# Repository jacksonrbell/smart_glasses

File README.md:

# Smart Translator Glasses
ECE 3332 - Microcontrollers Lab | Texas Tech University <br>
Jack Bell, Erik Longhenry, Brandon Runhaar

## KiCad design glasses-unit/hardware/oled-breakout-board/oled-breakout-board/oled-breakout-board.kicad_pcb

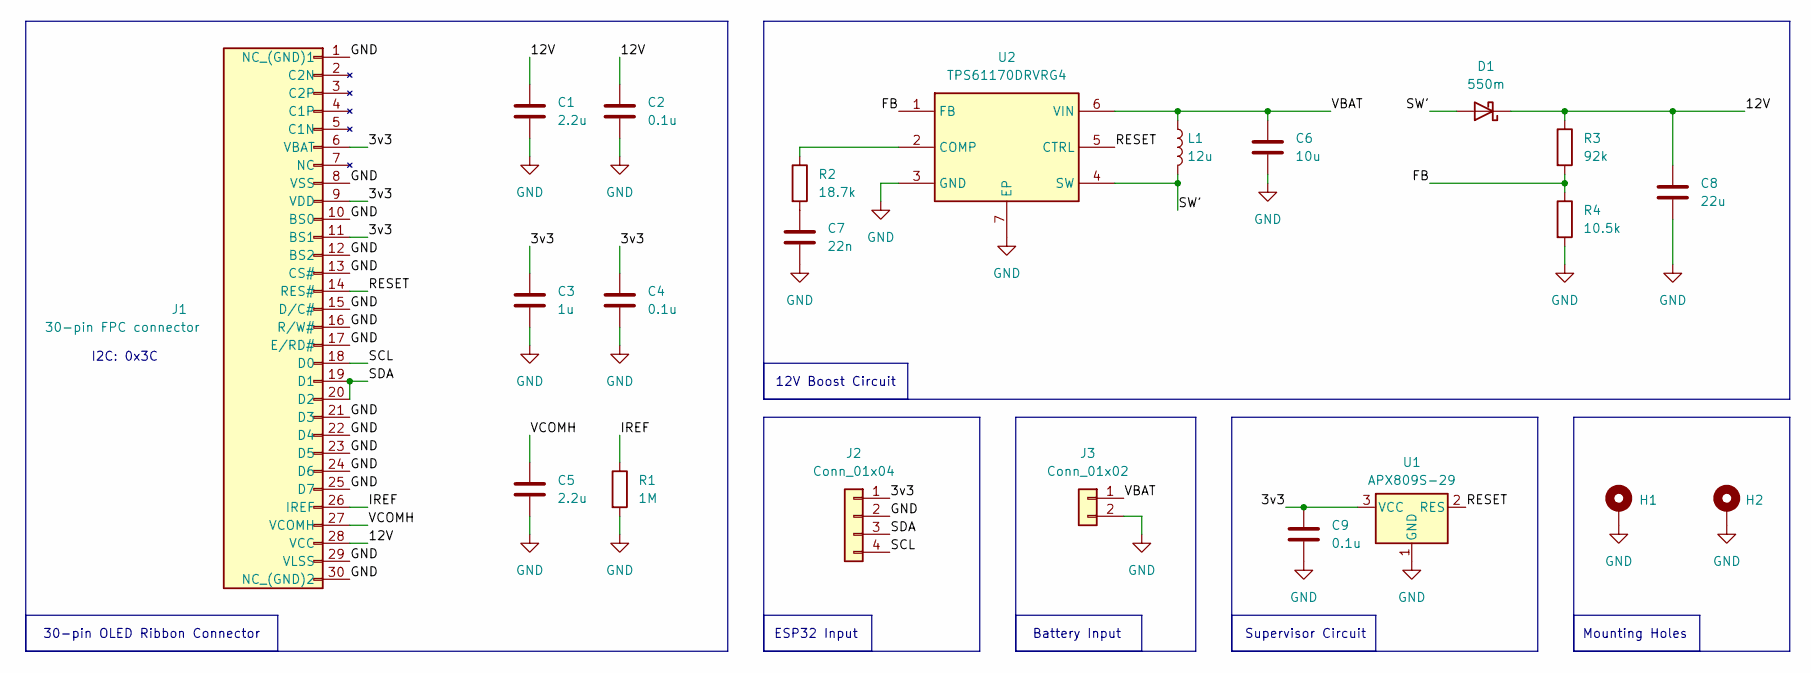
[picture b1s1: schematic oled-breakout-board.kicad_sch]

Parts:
C1, C5: 2.2u; C_1206_3216Metric_Pad1.33x1.80mm_HandSolder
C2, C4, C9: 0.1u; C_0603_1608Metric_Pad1.08x0.95mm_HandSolder
C3: 1u; C_0603_1608Metric_Pad1.08x0.95mm_HandSolder
C6: 10u; C_1206_3216Metric_Pad1.33x1.80mm_HandSolder
C7: 22n; C_0603_1608Metric_Pad1.08x0.95mm_HandSolder
C8: 22u; C_1206_3216Metric_Pad1.33x1.80mm_HandSolder
D1: 550m; D_SOD-123F
H1, H2: Mounting Hole; MountingHole_2.2mm_M2_Pad
J1: 30-pin FPC connector; 30-pin_fpc_connector_.7mm
J2: Conn_01x04; JST_PH_S4B-PH-SM4-TB_1x04-1MP_P2.00mm_Horizontal
J3: Conn_01x02; JST_PH_S2B-PH-SM4-TB_1x02-1MP_P2.00mm_Horizontal
L1: 12u; SRR4528A120M
R1: 1M; R_0603_1608Metric_Pad0.98x0.95mm_HandSolder
R2: 18.7k; R_0603_1608Metric_Pad0.98x0.95mm_HandSolder
R3: 92k; R_0603_1608Metric_Pad0.98x0.95mm_HandSolder
R4: 10.5k; R_0603_1608Metric_Pad0.98x0.95mm_HandSolder
U1: APX809S-29; TSOT-23
U2: TPS61170DRVRG4; SON65P200X200X80-7N; Mouser Part Number 595-TPS61170DRVRG4

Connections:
/3v3: C3.1, C4.1, C9.1, J1.6 (VBAT), J1.9 (VDD), J1.11 (BS1), J2.1, U1.3 (VCC)
/12V: C1.1, C2.1, C8.1, D1.1 (K), J1.28 (VCC), R3.1
/FB: R3.2, R4.1, U2.1 (FB)
/IREF: J1.26 (IREF), R1.1
/RESET: J1.14 (RES#), U1.2 (RES), U2.5 (CTRL)
/SCL: J1.18 (D0), J2.4
/SDA: J1.19 (D1), J1.20 (D2), J2.3
/SW': D1.2 (A), L1.2, U2.4 (SW)
/VBAT: C6.1, J3.1, L1.1, U2.6 (VIN)
/VCOMH: C5.1, J1.27 (VCOMH)
GND: C1.2, C2.2, C3.2, C4.2, C5.2, C6.2, C7.2, C8.2, C9.2, H1.1 (1_1), H2.1 (1_1), J1.1 (NC_(GND)1), J1.8 (VSS), J1.10 (BS0), J1.12 (BS2), J1.13 (CS#), J1.15 (D/C#), J1.16 (R/W#), J1.17 (E/RD#), J1.21 (D3), J1.22 (D4), J1.23 (D5), J1.24 (D6), J1.25 (D7), J1.29 (VLSS), J1.30 (NC_(GND)2), J2.2, J3.2, R1.2, R4.2, U1.1 (GND), U2.3 (GND), U2.7 (EP)
unnamed: C7.1, R2.2
unnamed: R2.1, U2.2 (COMP)

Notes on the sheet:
12V Boost Circuit
Mounting Holes
Supervisor Circuit
ESP32 Input
Battery Input
30-pin OLED Ribbon Connector
I2C: 0x3C

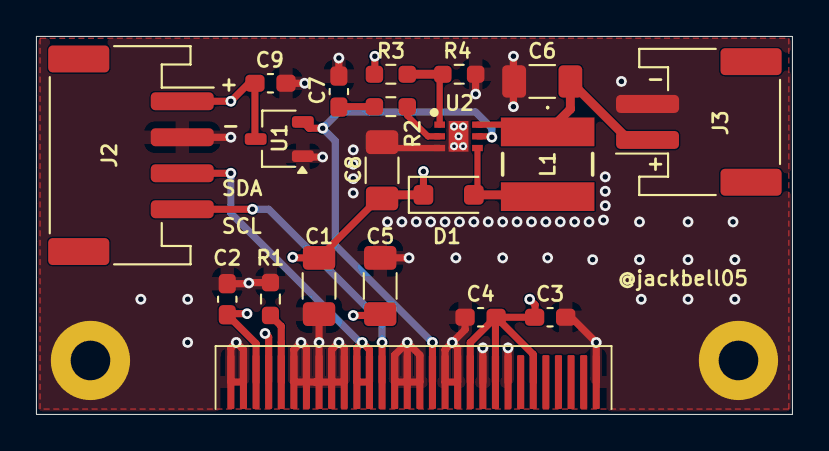
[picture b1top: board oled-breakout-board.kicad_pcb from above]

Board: 4 copper layers, 42.0 x 21.0 mm, 22 parts (0 on the bottom side), 13 nets.

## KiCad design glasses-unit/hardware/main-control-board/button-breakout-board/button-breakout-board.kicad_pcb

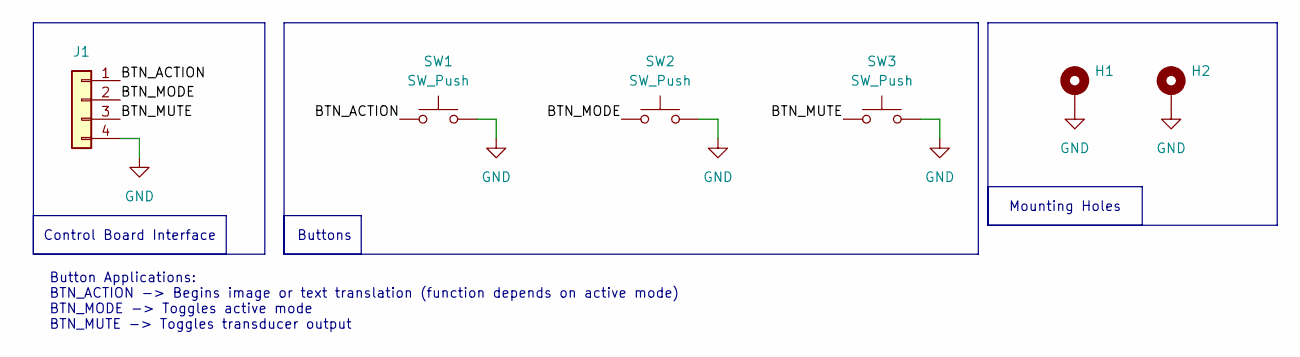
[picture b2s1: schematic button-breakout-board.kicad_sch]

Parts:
H1, H2: MountingHole_Pad; MountingHole_2.2mm_M2_Pad
J1: JST_PH_S4B-PH-SM4-TB_1x04-1MP_P2.00mm_Horizontal
SW1, SW2, SW3: SW_Push; SW_3983_ADA

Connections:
/BTN_ACTION: J1.1, SW1.1
/BTN_MODE: J1.2, SW2.1
/BTN_MUTE: J1.3, SW3.1
GND: H1.1 (1_1), H2.1 (1_1), J1.4, SW1.2, SW2.2, SW3.2

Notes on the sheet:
Control Board Interface
Buttons
Button Applications: BTN_ACTION -> Begins image or text translation (function depends on active mode) BTN_MODE -> Toggles active mode BTN_MUTE -> Toggles transducer output
Mounting Holes

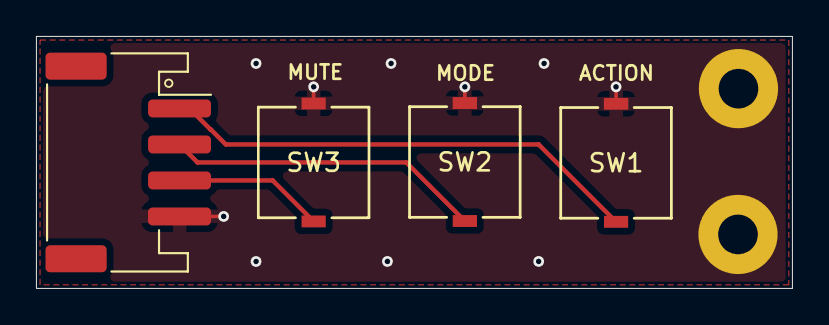
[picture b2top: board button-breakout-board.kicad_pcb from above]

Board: 2 copper layers, 42.0 x 14.0 mm, 6 parts (0 on the bottom side), 4 nets.

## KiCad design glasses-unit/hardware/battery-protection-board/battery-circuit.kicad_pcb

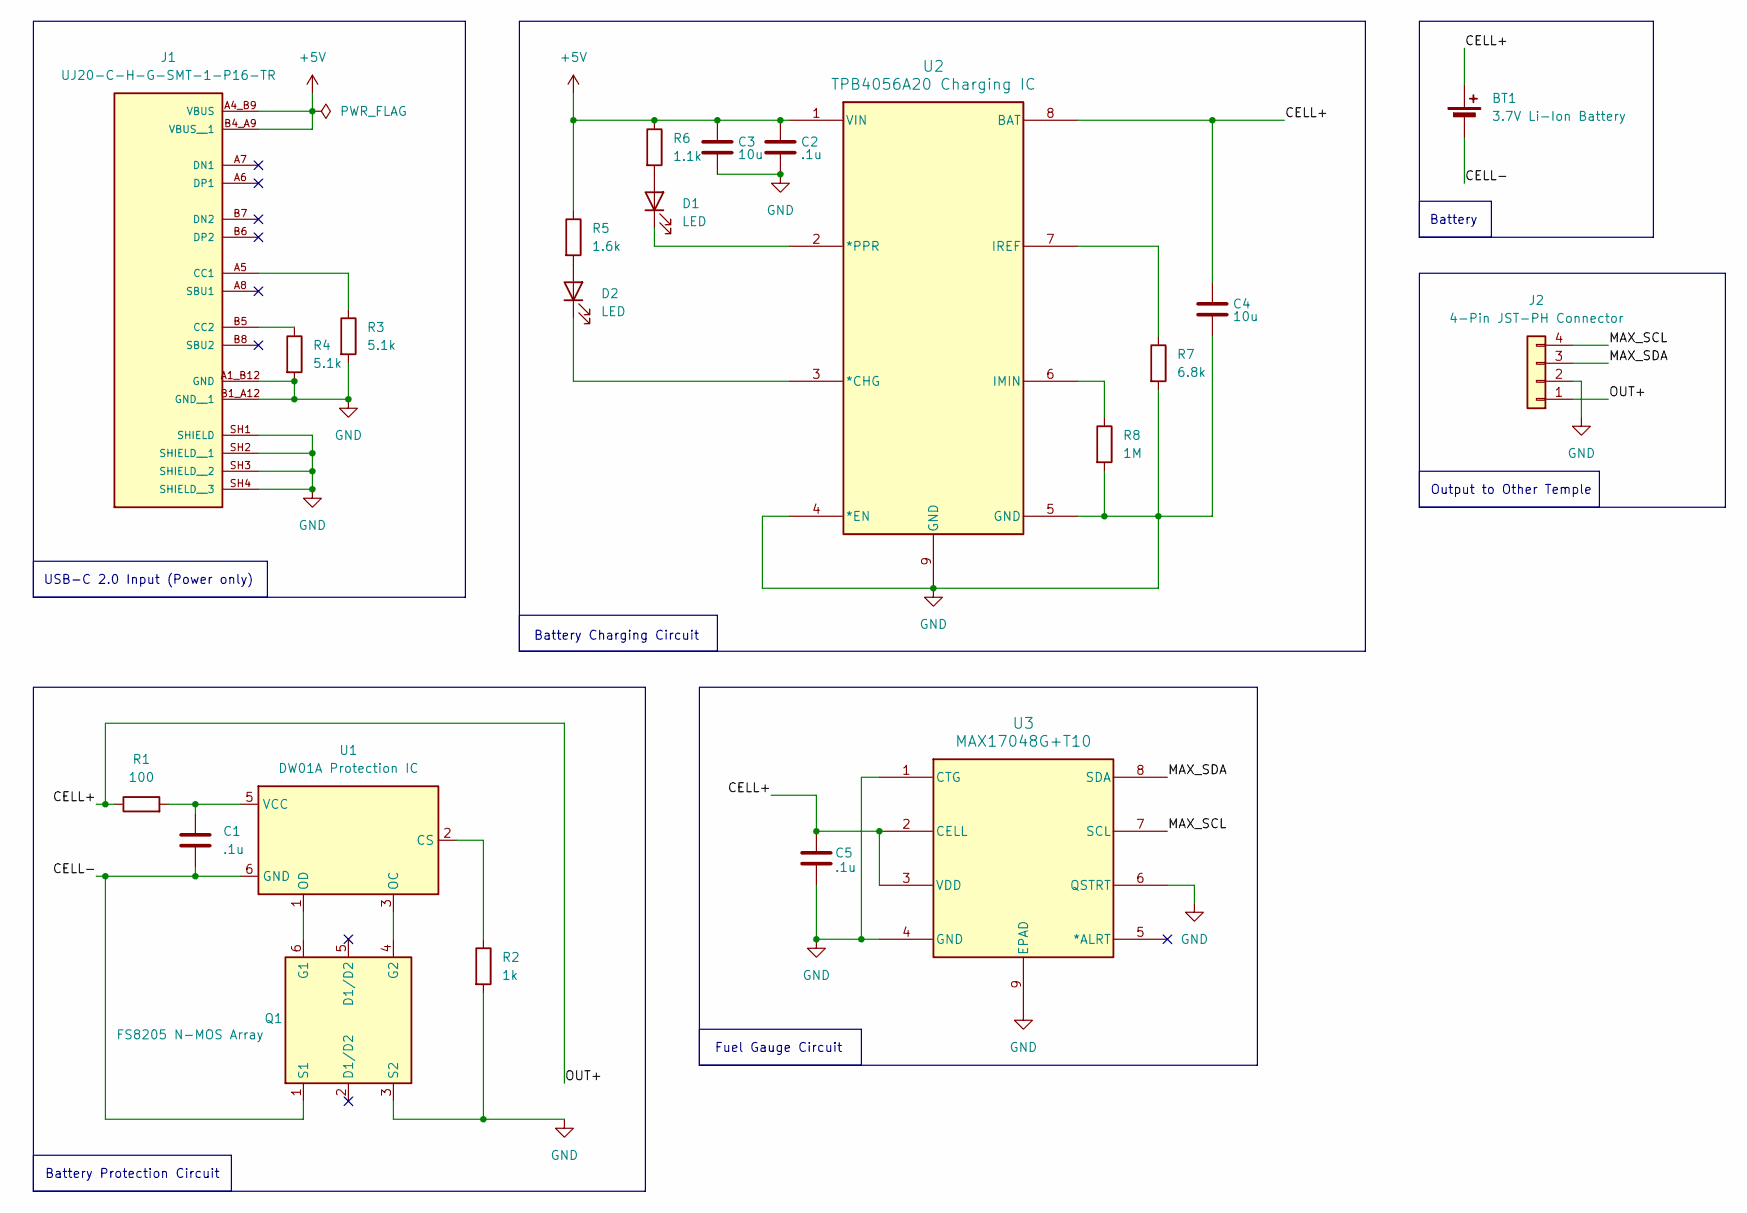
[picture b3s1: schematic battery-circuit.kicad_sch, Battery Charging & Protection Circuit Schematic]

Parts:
BT1: 3.7V Li-Ion Battery; JST_PH_S2B-PH-SM4-TB_1x02-1MP_P2.00mm_Horizontal
C1, C2, C5: .1u; C_0603_1608Metric_Pad1.08x0.95mm_HandSolder
C3, C4: 10u; C_0603_1608Metric_Pad1.08x0.95mm_HandSolder
D1, D2: LED; LED_0603_1608Metric_Pad1.05x0.95mm_HandSolder
J1: UJ20-C-H-G-SMT-1-P16-TR; usb-c 2.0 receptacle; PARTREV 1.0
J2: 4-Pin JST-PH Connector; JST_PH_S4B-PH-SM4-TB_1x04-1MP_P2.00mm_Horizontal
Q1: FS8205 N-MOS Array; SOT-23-6
R1: 100; R_0603_1608Metric_Pad0.98x0.95mm_HandSolder
R2: 1k; R_0603_1608Metric_Pad0.98x0.95mm_HandSolder
R3, R4: 5.1k; R_0603_1608Metric_Pad0.98x0.95mm_HandSolder
R5: 1.6k; R_0603_1608Metric_Pad0.98x0.95mm_HandSolder
R6: 1.1k; R_0603_1608Metric_Pad0.98x0.95mm_HandSolder
R7: 6.8k; R_0603_1608Metric_Pad0.98x0.95mm_HandSolder
R8: 1M; R_0603_1608Metric_Pad0.98x0.95mm_HandSolder
U1: DW01A Protection IC; SOT-23-6
U2: TPB4056A20 Charging IC; TPB4056A20-DFGR
U3: MAX17048G+T10; MAX17048G_T10

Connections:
+5V: C2.1, C3.1, J1.A4_B9 (VBUS), J1.B4_A9 (VBUS__1), R5.1, R6.1, U2.1 (VIN)
/CELL+: BT1.1 (+), C4.1, C5.1, J2.1, R1.1, U2.8 (BAT), U3.2 (CELL), U3.3 (VDD)
/CELL-: BT1.2 (-), C1.2, Q1.1 (S1), U1.6 (GND)
/MAX_SCL: J2.4, U3.7 (SCL)
/MAX_SDA: J2.3, U3.8 (SDA)
GND: C2.2, C3.2, C4.2, C5.2, J1.A1_B12 (GND), J1.B1_A12 (GND__1), J1.SH1 (SHIELD), J1.SH2 (SHIELD__1), J1.SH3 (SHIELD__2), J1.SH4 (SHIELD__3), J2.2, Q1.3 (S2), R2.2, R3.2, R4.2, R7.2, R8.2, U2.4 (*EN), U2.5 (GND), U2.9 (GND), U3.1 (CTG), U3.4 (GND), U3.6 (QSTRT), U3.9 (EPAD)
unnamed: D1.2 (A), R6.2
unnamed: D1.1 (K), U2.2 (*PPR)
unnamed: D2.2 (A), R5.2
unnamed: D2.1 (K), U2.3 (*CHG)
unnamed: J1.A5 (CC1), R3.1
unnamed: J1.B5 (CC2), R4.1
unnamed: Q1.6 (G1), U1.1 (OD)
unnamed: Q1.4 (G2), U1.3 (OC)
unnamed: R2.1, U1.2 (CS)
unnamed: C1.1, R1.2, U1.5 (VCC)
unnamed: R8.1, U2.6 (IMIN)
unnamed: R7.1, U2.7 (IREF)

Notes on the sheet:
Battery
Output to Other Temple
Fuel Gauge Circuit
USB-C 2.0 Input (Power only)
Battery Charging Circuit
Battery Protection Circuit

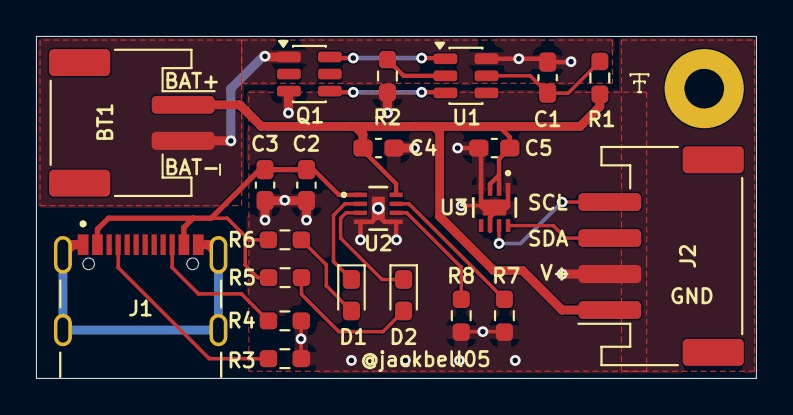
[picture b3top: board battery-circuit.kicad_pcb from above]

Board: 2 copper layers, 40.0 x 19.0 mm, 22 parts (0 on the bottom side), 18 nets.

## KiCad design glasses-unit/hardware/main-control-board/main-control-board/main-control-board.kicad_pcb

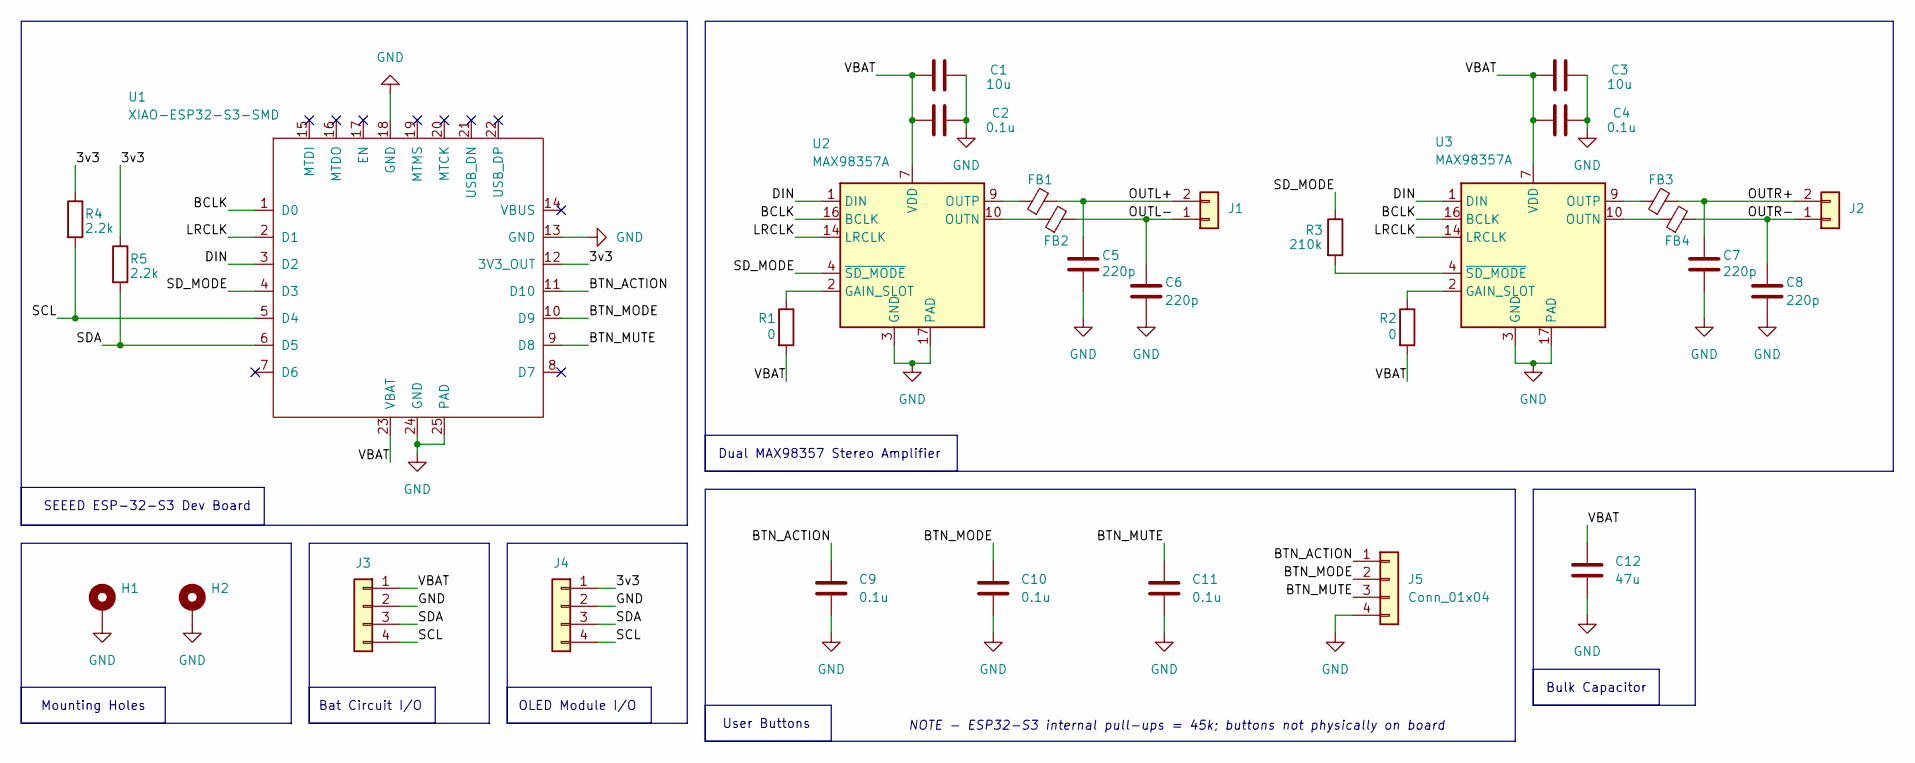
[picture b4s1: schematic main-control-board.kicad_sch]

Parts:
C1, C3: 10u; C_1206_3216Metric_Pad1.33x1.80mm_HandSolder
C2, C4, C9, C10, C11: 0.1u; C_0603_1608Metric_Pad1.08x0.95mm_HandSolder
C5, C6, C7, C8: 220p; C_0603_1608Metric_Pad1.08x0.95mm_HandSolder
C12: 47u; WCAP-ASLI_5X5.5_DXL_
FB1, FB2, FB3, FB4: FerriteBead_Small; C_0603_1608Metric_Pad1.08x0.95mm_HandSolder
H1, H2: MountingHole_Pad; MountingHole_2.2mm_M2_Pad
J1, J2: Conn_01x02; JST_PH_B2B-PH-SM4-TB_1x02-1MP_P2.00mm_Vertical
J3, J4, J5: Conn_01x04; JST_PH_B4B-PH-SM4-TB_1x04-1MP_P2.00mm_Vertical
R1, R2: 0; C_0603_1608Metric_Pad1.08x0.95mm_HandSolder
R3: 210k; C_0603_1608Metric_Pad1.08x0.95mm_HandSolder
R4, R5: 2.2k; C_0603_1608Metric_Pad1.08x0.95mm_HandSolder
U1: XIAO-ESP32-S3-SMD
U2, U3: MAX98357A; TQFN-16-1EP_3x3mm_P0.5mm_EP1.23x1.23mm

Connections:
/3v3: J4.1, R4.1, R5.1, U1.12 (3V3_OUT)
/BCLK: U1.1 (D0), U2.16 (BCLK), U3.16 (BCLK)
/BTN_ACTION: C9.1, J5.1, U1.11 (D10)
/BTN_MODE: C10.1, J5.2, U1.10 (D9)
/BTN_MUTE: C11.1, J5.3, U1.9 (D8)
/DIN: U1.3 (D2), U2.1 (DIN), U3.1 (DIN)
/LRCLK: U1.2 (D1), U2.14 (LRCLK), U3.14 (LRCLK)
/OUTL+: C5.1, FB1.2, J1.2
/OUTL-: C6.1, FB2.2, J1.1
/OUTR+: C7.1, FB3.2, J2.2
/OUTR-: C8.1, FB4.2, J2.1
/SCL: J3.4, J4.4, R4.2, U1.5 (D4)
/SDA: J3.3, J4.3, R5.2, U1.6 (D5)
/SD_MODE: R3.1, U1.4 (D3), U2.4 (~SD_MODE)
/VBAT: C1.2, C2.2, C3.2, C4.2, C12.1, J3.1, R1.2, R2.2, U1.23 (VBAT), U2.7 (VDD), U2.8 (VDD), U3.7 (VDD), U3.8 (VDD)
GND: C1.1, C2.1, C3.1, C4.1, C5.2, C6.2, C7.2, C8.2, C9.2, C10.2, C11.2, C12.2, H1.1 (1_1), H2.1, J3.2, J4.2, J5.4, U1.13 (GND), U1.18 (GND), U1.24 (GND), U1.25 (PAD), U2.3 (GND), U2.11 (GND), U2.15 (GND), U2.17 (PAD), U3.3 (GND), U3.11 (GND), U3.15 (GND), U3.17 (PAD)
unnamed: R1.1, U2.2 (GAIN_SLOT)
unnamed: FB2.1, U2.10 (OUTN)
unnamed: FB1.1, U2.9 (OUTP)
unnamed: R2.1, U3.2 (GAIN_SLOT)
unnamed: FB4.1, U3.10 (OUTN)
unnamed: FB3.1, U3.9 (OUTP)
unnamed: R3.2, U3.4 (~SD_MODE)

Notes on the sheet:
NOTE - ESP32-S3 internal pull-ups = 45k; buttons not physically on board
Bulk Capacitor
Bat Circuit I/O
Dual MAX98357 Stereo Amplifier
User Buttons
Mounting Holes
OLED Module I/O
SEEED ESP-32-S3 Dev Board

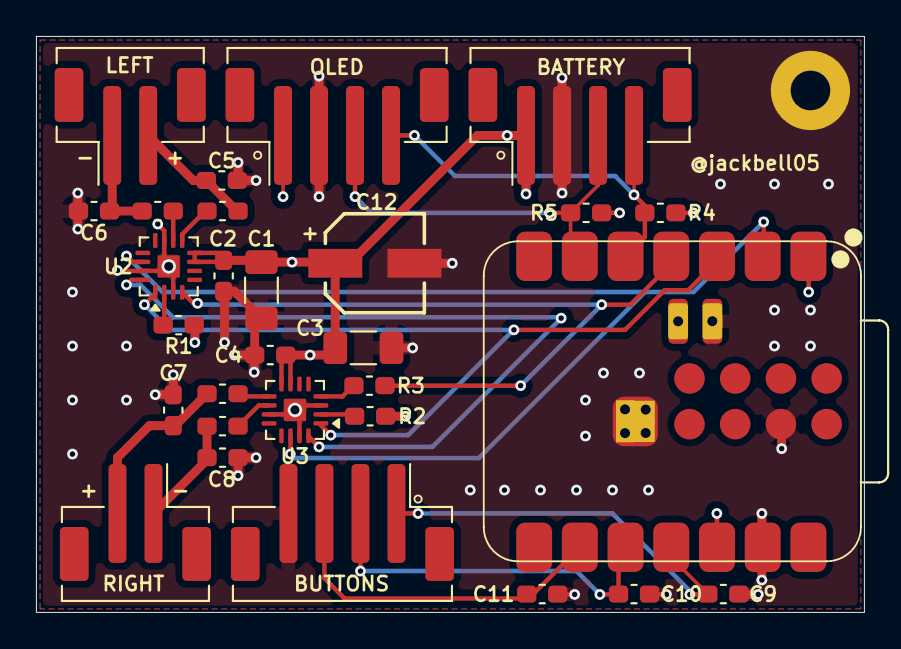
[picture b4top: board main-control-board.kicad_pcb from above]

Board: 4 copper layers, 46.0 x 32.0 mm, 30 parts (0 on the bottom side), 23 nets.

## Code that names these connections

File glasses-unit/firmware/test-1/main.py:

# main.py - Glasses unit first power-on test (with file logging)
# Target: Seeed XIAO ESP32S3 Sense, MicroPython (ESP32_GENERIC_S3 build)
# Requires: ssd1306.py driver on the board (Thonny: Tools > Manage packages > "ssd1306")
# Log: /log.txt on the board's flash (previous log rotated to /log_old.txt)

from machine import Pin, I2C, I2S
import machine, time, math, struct, os, sys, io

# ---------------- 1. Mute amps immediately ----------------
PIN_SD_MODE = 4                            # D3 (low = both amps shutdown/mute)
sd_mode = Pin(PIN_SD_MODE, Pin.OUT, value=0)

# ---------------- Settings ----------------
STARTUP_HOLD_MS = 1000     # settle time after power switch before init
BATT_POLL_MS    = 2000     # MAX17048 polling interval
BUZZ_PERIOD_MS  = 5000     # buzz every 5 s
BUZZ_MS         = 200      # buzz length
BUZZ_FREQ       = 441      # Hz (exactly 50 samples/cycle at 22.05 kHz)
BUZZ_AMP        = 8000     # 16-bit peak (~-12 dBFS); raise for louder
I2C_FREQ        = 100_000  # conservative for first bring-up
AUDIO_RATE      = 22050
I2S_IBUF        = 8000     # bytes (~90 ms of 16-bit stereo at 22.05 kHz)

LOG_FILE     = "/log.txt"
LOG_OLD      = "/log_old.txt"
LOG_MAX      = 64 * 1024   # bytes before rotating
BOOTCOUNT    = "/bootcount.txt"

# ---------------- Pin map (control PCB, Oct 21 2026) ----------------
PIN_BCLK, PIN_LRCLK, PIN_DIN = 1, 2, 3     # D0, D1, D2
PIN_SCL, PIN_SDA = 5, 6                    # D4, D5
PIN_BTN_MUTE, PIN_BTN_MODE, PIN_BTN_ACTION = 7, 8, 9   # D8, D9, D10

MAX17048_ADDR = 0x36
OLED_ADDRS = (0x3C, 0x3D)

# ---------------- Logging ----------------
def _rotate():
    try:
        if os.stat(LOG_FILE)[6] > LOG_MAX:
            try:
                os.remove(LOG_OLD)
            except OSError:
                pass
            os.rename(LOG_FILE, LOG_OLD)
    except OSError:
        pass  # no log yet

def log(msg):
    line = "%9d ms | %s" % (time.ticks_ms(), msg)
    print(line)
    try:
        with open(LOG_FILE, "a") as f:   # open/close each line: survives power-off
            f.write(line + "\n")
    except OSError as e:
        print("LOG WRITE FAILED:", e)

def log_exception(e):
    buf = io.StringIO()
    sys.print_exception(e, buf)
    log("EXCEPTION:\n" + buf.getvalue())

def next_boot_number():
    n = 0
    try:
        with open(BOOTCOUNT) as f:
            n = int(f.read())
    except (OSError, ValueError):
        pass
    n += 1
    try:
        with open(BOOTCOUNT, "w") as f:
            f.write(str(n))
    except OSError:
        pass
    return n

RESET_NAMES = {
    machine.PWRON_RESET: "PWRON",
    machine.HARD_RESET: "HARD",
    machine.WDT_RESET: "WDT",
    machine.DEEPSLEEP_RESET: "DEEPSLEEP",
    machine.SOFT_RESET: "SOFT",
}

_rotate()
log("===== BOOT %d | reset cause: %s =====" % (
    next_boot_number(),
    RESET_NAMES.get(machine.reset_cause(), str(machine.reset_cause()))))
log("Amps muted (SD_MODE low)")

i2s = None
try:
    # ---------------- 2. Button pull-ups ----------------
    btn_mute   = Pin(PIN_BTN_MUTE,   Pin.IN, Pin.PULL_UP)
    btn_mode   = Pin(PIN_BTN_MODE,   Pin.IN, Pin.PULL_UP)
    btn_action = Pin(PIN_BTN_ACTION, Pin.IN, Pin.PULL_UP)
    log("Button pull-ups enabled (D8-D10)")

    # ---------------- 3. Startup hold ----------------
    time.sleep_ms(STARTUP_HOLD_MS)
    log("Startup hold done (%d ms)" % STARTUP_HOLD_MS)

    # ---------------- 4. I2C + device discovery ----------------
    i2c = I2C(0, sda=Pin(PIN_SDA), scl=Pin(PIN_SCL), freq=I2C_FREQ)
    found = i2c.scan()
    log("I2C scan: %s" % [hex(a) for a in found])

    gauge_ok = MAX17048_ADDR in found
    log("MAX17048 (0x36): %s" % ("found" if gauge_ok else "NOT FOUND"))

    oled = None
    oled_addr = next((a for a in OLED_ADDRS if a in found), None)
    if oled_addr is None:
        log("OLED (0x3C/0x3D): NOT FOUND")
    else:
        try:
            import ssd1306
            # external_vcc=True: internal charge pump disabled (12V VCC from external converter)
            oled = ssd1306.SSD1306_I2C(128, 64, i2c, addr=oled_addr, external_vcc=True)
            oled.fill(0)
            oled.text("TEST", 48, 8)
            oled.show()
            log("OLED OK at %s, wrote TEST" % hex(oled_addr))
        except Exception as e:
            log("OLED init failed")
            log_exception(e)
            oled = None

    def read_soc():
        d = i2c.readfrom_mem(MAX17048_ADDR, 0x04, 2)   # SOC register
        return d[0] + d[1] / 256                         # percent

    def show_batt(text):
        if oled is None:
            return
        oled.fill_rect(0, 32, 128, 16, 0)
        oled.text(text, 0, 32)
        oled.show()

    # ---------------- 5. I2S + buzz buffers ----------------
    i2s = I2S(0, sck=Pin(PIN_BCLK), ws=Pin(PIN_LRCLK), sd=Pin(PIN_DIN),
              mode=I2S.TX, bits=16, format=I2S.STEREO,
              rate=AUDIO_RATE, ibuf=I2S_IBUF)
    log("I2S init OK (%d Hz, 16-bit stereo)" % AUDIO_RATE)

    period = AUDIO_RATE // BUZZ_FREQ                 # samples per cycle
    cycle = bytearray(period * 4)
    for n in range(period):
        s = int(BUZZ_AMP * math.sin(2 * math.pi * n / period))
        struct.pack_into("<hh", cycle, n * 4, s, s)  # L, R identical
    reps = max(1, BUZZ_MS * BUZZ_FREQ // 1000)
    tone = bytearray(len(cycle) * reps)
    for r in range(reps):
        tone[r * len(cycle):(r + 1) * len(cycle)] = cycle

    lead_silence = bytearray(int(AUDIO_RATE * 0.02) * 4)    # 20 ms (amp turn-on ~7 ms)
    tail_silence = bytearray(I2S_IBUF + 4 * 512)            # flush buffer with zeros
    drain_ms = int(len(tail_silence) / (AUDIO_RATE * 4) * 1000) + 30

    def buzz():
        sd_mode.value(1)            # unmute
        i2s.write(lead_silence)
        i2s.write(tone)
        i2s.write(tail_silence)
        time.sleep_ms(drain_ms)     # let queued audio finish
        sd_mode.value(0)            # mute

    # ---------------- 6. Main loop ----------------
    log("Entering main loop")
    next_batt = time.ticks_ms()
    next_buzz = time.ticks_add(time.ticks_ms(), BUZZ_PERIOD_MS)
    buzz_count = 0

    while True:
        now = time.ticks_ms()

        if time.ticks_diff(now, next_batt) >= 0:
            next_batt = time.ticks_add(now, BATT_POLL_MS)
            if gauge_ok:
                try:
                    soc = read_soc()
                    log("Battery: %.1f%%" % soc)
                    show_batt("BAT: %d%%" % int(soc))
                except OSError as e:
                    log("Gauge read failed: %s" % e)
                    show_batt("BAT: ERR")
            else:
                show_batt("BAT: N/A")

        if time.ticks_diff(now, next_buzz) >= 0:
            next_buzz = time.ticks_add(now, BUZZ_PERIOD_MS)
            buzz_count += 1
            buzz()
            log("Buzz #%d" % buzz_count)

        time.sleep_ms(20)

except KeyboardInterrupt:
    log("Stopped by user (Ctrl-C)")
except Exception as e:
    log("FATAL")
    log_exception(e)
finally:
    sd_mode.value(0)
    if i2s is not None:
        i2s.deinit()
    log("Amps muted, exiting")
